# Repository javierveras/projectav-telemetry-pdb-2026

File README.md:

# Telemetry & Power Distribution System
Our power distribution and telemetry system's hardware, firmware, and technical documentation.

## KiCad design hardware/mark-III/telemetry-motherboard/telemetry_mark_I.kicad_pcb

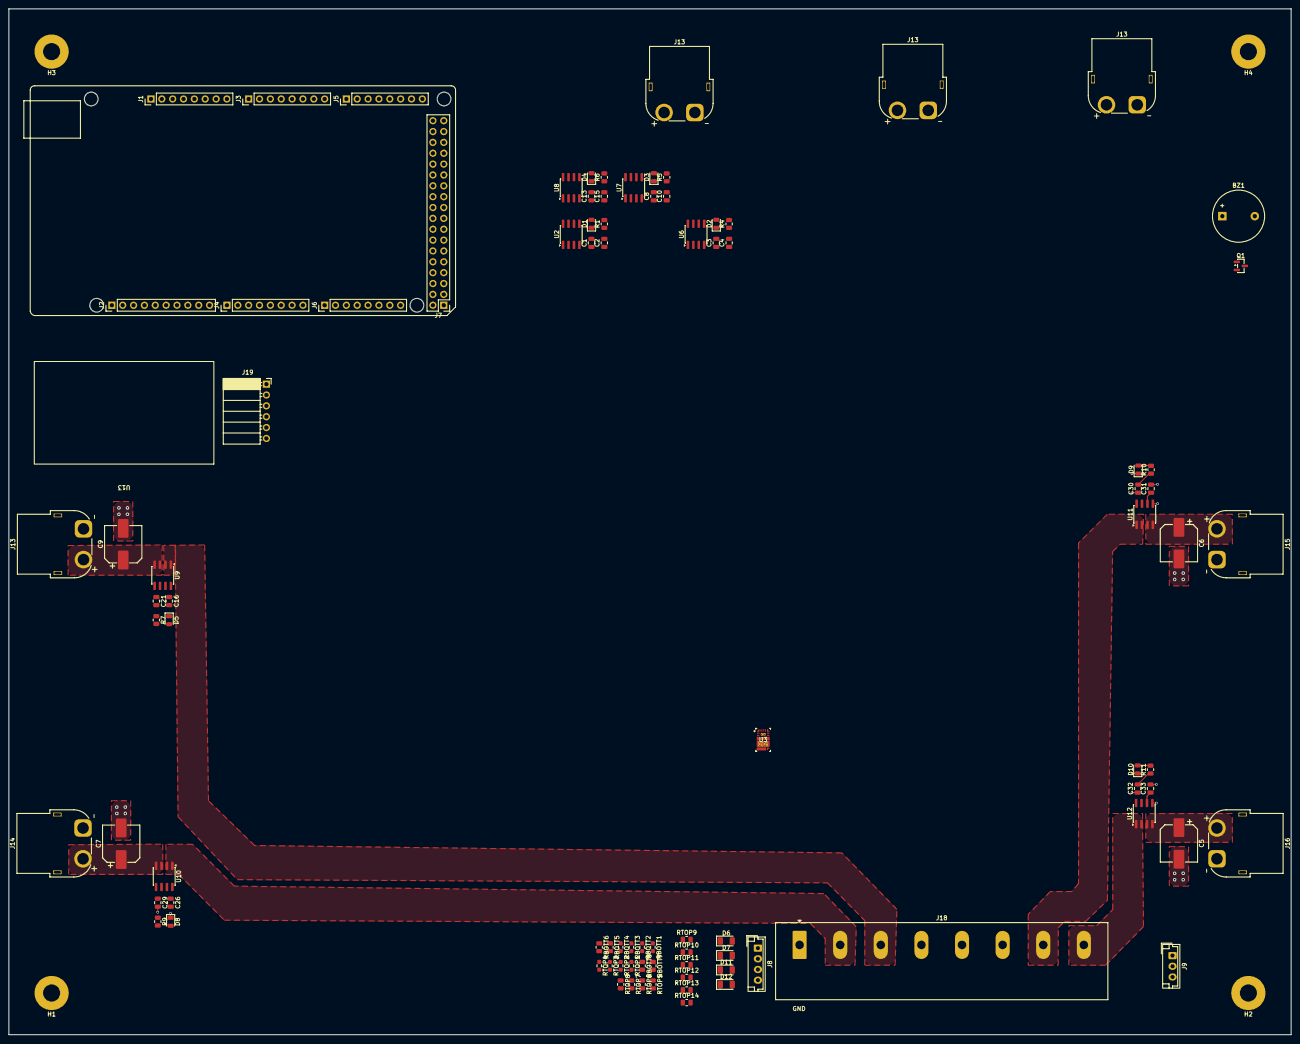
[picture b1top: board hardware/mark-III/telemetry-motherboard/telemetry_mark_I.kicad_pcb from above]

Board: 4 copper layers, 300.0 x 240.0 mm, 101 parts (0 on the bottom side), 58 nets.

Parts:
BZ1: Buzzer; Buzzer_12x9.5RM7.6
C1, C3, C8, C13, C16, C26, C30, C32: 100nF; C_0805_2012Metric
C2, C4, C10, C15, C21, C29, C31, C33: 1nF; C_0805_2012Metric
C5, C6, C7, C9: C_Polarized; CP_Elec_8x10.5
D1, D2, D3, D4, D5, D8, D9, D10: LED; LED_0805_2012Metric
D6, D7, D11, D12: LED; LED_1206_3216Metric
H1, H2, H3, H4: MountingHole; MountingHole_4mm_Pad
J1: Power; PinHeader_1x08_P2.54mm_Vertical
J2: PWM; PinHeader_1x10_P2.54mm_Vertical
J3, J5: Analog; PinHeader_1x08_P2.54mm_Vertical
J4: PWM; PinHeader_1x08_P2.54mm_Vertical
J6: Communication; PinHeader_1x08_P2.54mm_Vertical
J7: Digital; PinHeader_2x18_P2.54mm_Vertical
J8: INPUT_CELL1; JST_EH_B4B-EH-A_1x04_P2.50mm_Vertical
J9: Temp_Sensor_Header; JST_EH_B3B-EH-A_1x03_P2.50mm_Vertical
J13, J13#2, J13#3, J13#4, J14, J15, J16: Conn_01x02_Socket; AMASS_XT60PW-F_1x02_P7.20mm_Horizontal
J18: Screw_Terminal_01x08; TerminalBlock_Ningbo-Kagnex_HB9500_1x08_P9.5mm
J19: Conn_01x06_Pin; PinSocket_1x06_P2.54mm_Horizontal
MH1, MH2, MH5, MH6: MountingHole_3.2mm
Q1: Q_NPN_BEC; SOT-23
R1, R4, R5, R6, R7, R9, R10, R11: 1k; R_0805_2012Metric
RBOTT1, RBOTT2, RBOTT3, RBOTT4: 2k; R_0603_1608Metric_Pad0.98x0.95mm_HandSolder
RBOTT5, RBOTT6, RBOTT7, RBOTT8: 10K; R_0805_2012Metric
RTOP1, RTOP2, RTOP3, RTOP4: 18k; R_0603_1608Metric_Pad0.98x0.95mm_HandSolder
RTOP5, RTOP6, RTOP7, RTOP8: 47K; R_0805_2012Metric
RTOP9, RTOP12, RTOP13, RTOP14: 680; R_0805_2012Metric
RTOP10: 1k; R_0805_2012Metric
RTOP11: 10k; R_0805_2012Metric
U1: ArduinoMega
U2, U6, U7, U8, U9, U10, U11, U12: ACS712xLCTR-05B; SOIC-8_3.9x4.9mm_P1.27mm
U3: TPS543B25VRYSR; RYS0017A-MFG
U13: Untitled_3

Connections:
5V_MEASS: J9.1, RTOP4.1, U2.3 (IP-), U2.4 (IP-)
12V_MEASS: RTOP1.1, U6.3 (IP-), U6.4 (IP-)
24V_MEASS: RTOP2.1, U7.3 (IP-), U7.4 (IP-)
+5V: C1.2, C3.2, C8.2, C13.2, C16.2, C26.2, C30.2, C32.2, J1.5, J7.35, J7.36, R1.1, R4.1, R5.1, R6.1, R7.1, R9.1, R10.1, R11.1, U2.1 (IP+), U2.2 (IP+), U2.8 (VCC), U6.8 (VCC), U7.8 (VCC), U8.8 (VCC), U9.8 (VCC), U10.8 (VCC), U11.8 (VCC), U12.8 (VCC)
/5V_CURRENT: J3.1, U2.7 (VIOUT)
/5V_VOLTAGE: RBOTT4.1, RTOP4.2
/12V_CURRENT: J3.2, U6.7 (VIOUT)
/12V_VOLTAGE: RBOTT1.1, RTOP1.2
/24V_CURRENT: J3.3, U7.7 (VIOUT)
/24V_VOLTAGE: RBOTT2.1, RTOP2.2
/+12V: U6.1 (IP+), U6.2 (IP+)
/+24V: U7.1 (IP+), U7.2 (IP+)
/BATT_CURRENT: J3.4, U8.7 (VIOUT)
/BATT_VOLTAGE: RBOTT3.1, RTOP3.2
/BMS/MEASS_CELL1: RBOTT5.1, RTOP5.2
/BMS/MEASS_CELL2: RBOTT7.1, RTOP7.2
/BMS/MEASS_CELL3: RBOTT6.1, RTOP6.2
/BMS/MEASS_CELL4: RBOTT8.1, RTOP8.2
/RAW_BATT(15-ESCs): U8.1 (IP+), U8.2 (IP+)
/RAW_BATT(15-W1): J18.3, U9.1 (IP+), U9.2 (IP+)
/RAW_BATT(15-W2): J18.2, U10.1 (IP+), U10.2 (IP+)
/RAW_BATT(15-W3): J18.7, U11.1 (IP+), U11.2 (IP+)
/RAW_BATT(15-W4): J18.8, U12.1 (IP+), U12.2 (IP+)
/SCL/21: J2.1, J6.8
/SDA/20: J2.2, J6.7
/TEMP_READING: J3.5, J9.2
/W1_MEASS: C9.1, J13.2, J13#4.2, U9.3 (IP-), U9.4 (IP-)
/W2_MEASS: C7.1, J14.2, U10.3 (IP-), U10.4 (IP-)
/W3_MEASS: C6.1, J15.2, U11.3 (IP-), U11.4 (IP-)
/W4_MEASS: C5.1, J16.2, U12.3 (IP-), U12.4 (IP-)
BATT_MEASS: RTOP3.1, U8.3 (IP-), U8.4 (IP-)
GND: C1.1, C2.2, C3.1, C4.2, C5.2, C6.2, C7.2, C8.1, C9.2, C10.2, C13.1, C15.2, C16.1, C21.2, C26.1, C29.2, C30.1, C31.2, C32.1, C33.2, D1.1 (K), D2.1 (K), D3.1 (K), D4.1 (K), D5.1 (K), D6.1 (K), D7.1 (K), D8.1 (K), D9.1 (K), D10.1 (K), D11.1 (K), D12.1 (K), J1.6, J1.7, J2.4, J7.1, J7.2, J9.3, J13.1, J13#4.1, J14.1, J15.1, J16.1, J18.1, Q1.2 (E), RBOTT1.2, RBOTT2.2, RBOTT3.2, RBOTT4.2, RBOTT5.2, RBOTT6.2, RBOTT7.2, RBOTT8.2, RTOP11.1, U2.5 (GND), U6.5 (GND), U7.5 (GND), U8.5 (GND), U9.5 (GND), U10.5 (GND), U11.5 (GND), U12.5 (GND)
unnamed: BZ1.2 (-), Q1.3 (C)
unnamed: D1.2 (A), R1.2
unnamed: D2.2 (A), R4.2
unnamed: D3.2 (A), R5.2
unnamed: D4.2 (A), R6.2
unnamed: D5.2 (A), R7.2
unnamed: D6.2 (A), RTOP9.2
unnamed: D7.2 (A), RTOP13.2
unnamed: D8.2 (A), R9.2
unnamed: D9.2 (A), R10.2
unnamed: D10.2 (A), R11.2
unnamed: D11.2 (A), RTOP12.2
unnamed: D12.2 (A), RTOP14.2
unnamed: Q1.1 (B), RTOP10.2, RTOP11.2
unnamed: C2.1, U2.6 (FILTER)
unnamed: C4.1, U6.6 (FILTER)
unnamed: C10.1, U7.6 (FILTER)
unnamed: C15.1, U8.6 (FILTER)
unnamed: C21.1, U9.6 (FILTER)
unnamed: C29.1, U10.6 (FILTER)
unnamed: C31.1, U11.6 (FILTER)
unnamed: C33.1, U12.6 (FILTER)
RAW_CELL1: J8.1, RTOP5.1
RAW_CELL2: J8.2, RTOP7.1
RAW_CELL3: J8.3, RTOP6.1
RAW_CELL4: J8.4, RTOP8.1

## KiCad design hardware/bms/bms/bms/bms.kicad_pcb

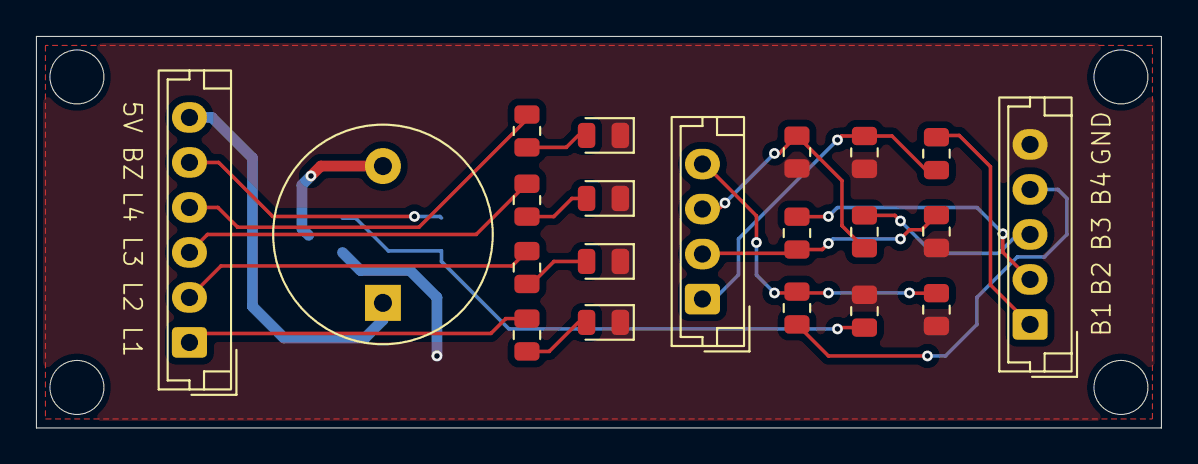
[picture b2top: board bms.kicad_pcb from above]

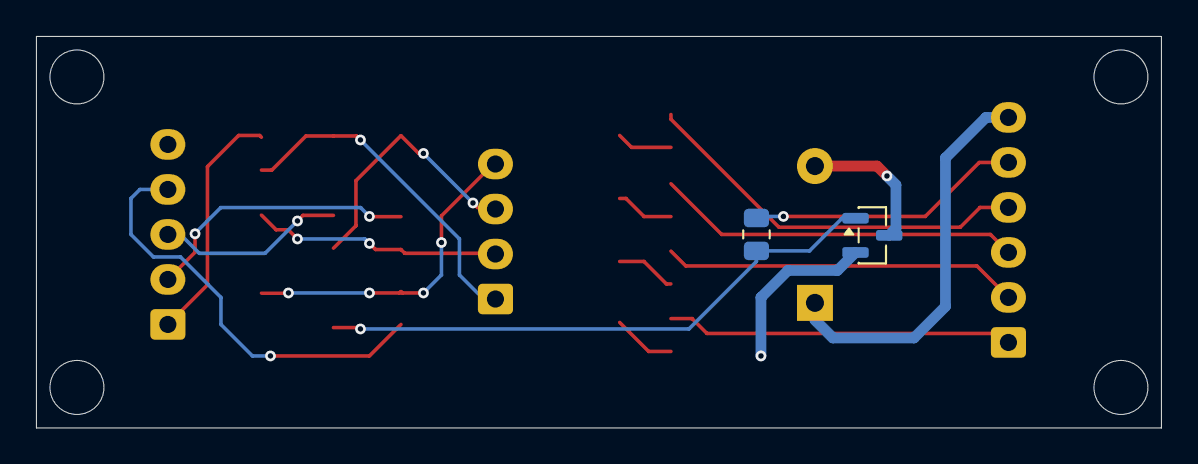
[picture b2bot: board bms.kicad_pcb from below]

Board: 2 copper layers, 62.5 x 21.8 mm, 23 parts (2 on the bottom side), 21 nets.

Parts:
BZ1: Buzzer; Buzzer_12x9.5RM7.6
D1, D2, D3, D4: LED; LED_0805_2012Metric
J1: OUTPUT; JST_EH_B4B-EH-A_1x04_P2.50mm_Vertical
J2: Conn_01x05_Pin; JST_EH_B5B-EH-A_1x05_P2.50mm_Vertical
J3: Conn_01x06_Pin; JST_EH_B6B-EH-A_1x06_P2.50mm_Vertical
Q1: Q_NPN_BEC; SOT-23
RBOTT5, RBOTT6, RBOTT7, RBOTT8: 10K; R_0805_2012Metric
RTOP5, RTOP6, RTOP7, RTOP8: 47K; R_0805_2012Metric
RTOP9, RTOP12, RTOP13, RTOP14: 680; R_0805_2012Metric
RTOP10: 1k; R_0805_2012Metric
RTOP11: 10k; R_0805_2012Metric

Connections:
/5V: BZ1.1 (+), J3.6
/BUZZER_GATE: J3.5, RTOP10.1
/LED1: J3.1, RTOP9.1
/LED2: J3.2, RTOP13.1
/LED3: J3.3, RTOP14.1
/LED4: J3.4, RTOP12.1
/MEASS_CELL1: J1.1, RBOTT5.1, RTOP5.2
/MEASS_CELL2: J1.2, RBOTT7.1, RTOP7.2
/MEASS_CELL3: J1.3, RBOTT6.1, RTOP6.2
/MEASS_CELL4: J1.4, RBOTT8.1, RTOP8.2
GND: D1.1 (K), D2.1 (K), D3.1 (K), D4.1 (K), J2.5, Q1.2 (E), RBOTT5.2, RBOTT6.2, RBOTT7.2, RBOTT8.2, RTOP11.1
unnamed: BZ1.2 (-), Q1.3 (C)
unnamed: D1.2 (A), RTOP9.2
unnamed: D2.2 (A), RTOP12.2
unnamed: D3.2 (A), RTOP13.2
unnamed: D4.2 (A), RTOP14.2
unnamed: Q1.1 (B), RTOP10.2, RTOP11.2
RAW_CELL1: J2.1, RTOP5.1
RAW_CELL2: J2.2, RTOP7.1
RAW_CELL3: J2.3, RTOP6.1
RAW_CELL4: J2.4, RTOP8.1

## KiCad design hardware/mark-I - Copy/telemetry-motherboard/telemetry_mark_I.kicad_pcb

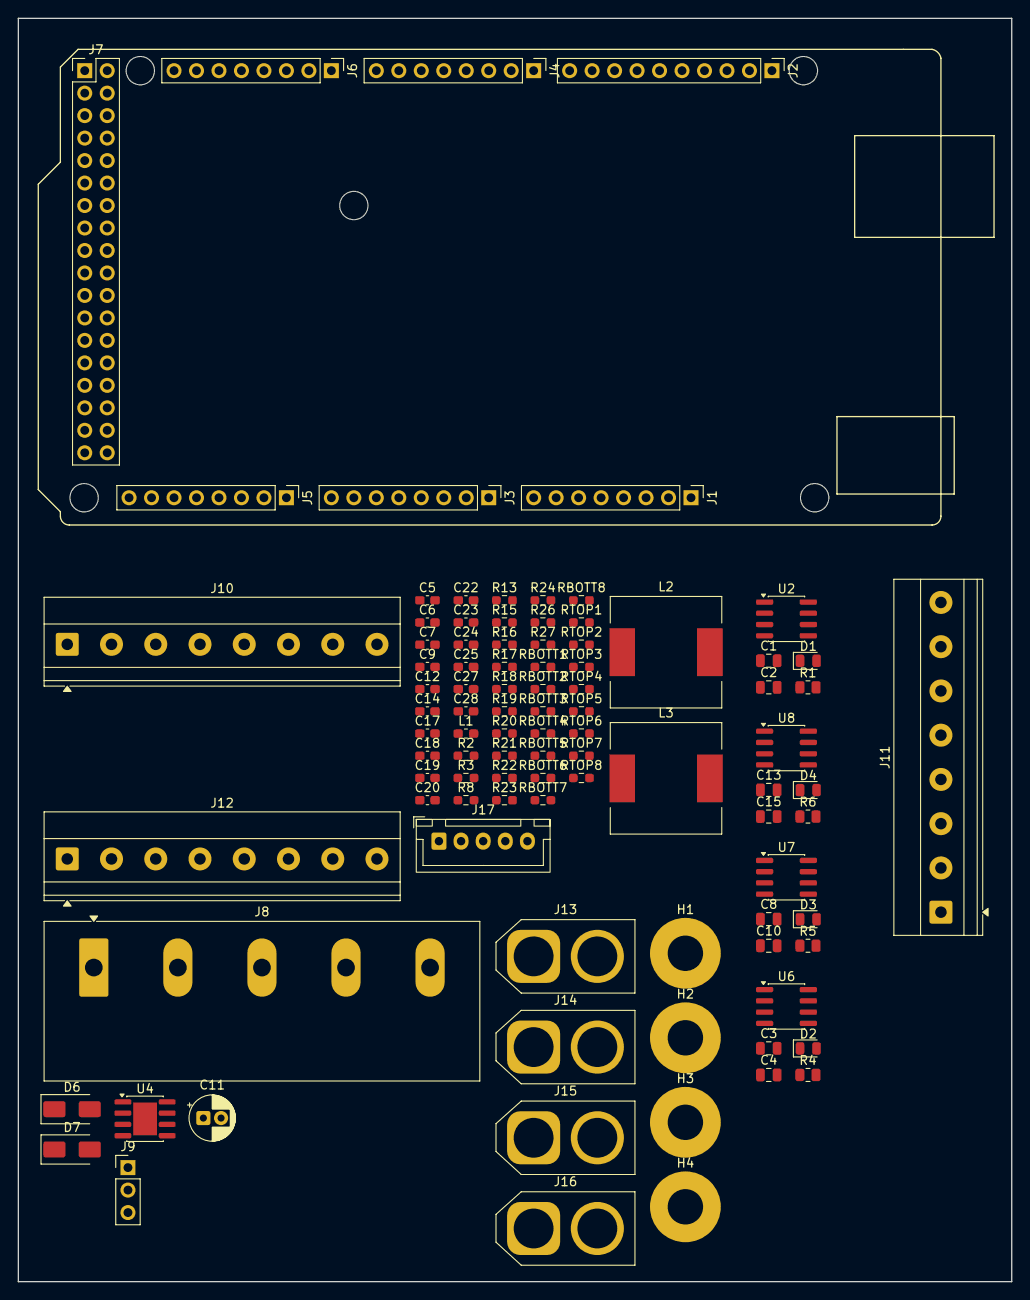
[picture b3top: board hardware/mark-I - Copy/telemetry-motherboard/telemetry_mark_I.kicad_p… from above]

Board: 2 copper layers, 112.2 x 142.8 mm, 101 parts (0 on the bottom side), 56 nets, no tracks yet.

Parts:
C1, C3, C8, C13: 100nF; C_0805_2012Metric
C2, C4, C10, C15: 1nF; C_0805_2012Metric
C5, C6: 68n; C_0603_1608Metric_Pad1.08x0.95mm_HandSolder
C7: 33n; C_0603_1608Metric_Pad1.08x0.95mm_HandSolder
C9: 4.7u; C_0603_1608Metric_Pad1.08x0.95mm_HandSolder
C11: 30u; CP_Radial_D5.0mm_P2.00mm
C12, C17, C19, C27, C28: 10u; C_0603_1608Metric_Pad1.08x0.95mm_HandSolder
C14: 4.7n; C_0603_1608Metric_Pad1.08x0.95mm_HandSolder
C18, C20: 0.3n; C_0603_1608Metric_Pad1.08x0.95mm_HandSolder
C22, C23: 1n; C_0603_1608Metric_Pad1.08x0.95mm_HandSolder
C24, C25: 100n; C_0603_1608Metric_Pad1.08x0.95mm_HandSolder
D1, D2, D3, D4: LED; LED_0805_2012Metric
D6, D7: SS54; D_SMA
H1, H2, H3, H4: MountingHole; MountingHole_4mm_Pad
J1: Power; PinHeader_1x08_P2.54mm_Vertical
J2: PWM; PinHeader_1x10_P2.54mm_Vertical
J3, J5: Analog; PinHeader_1x08_P2.54mm_Vertical
J4: PWM; PinHeader_1x08_P2.54mm_Vertical
J6: Communication; PinHeader_1x08_P2.54mm_Vertical
J7: Digital; PinHeader_2x18_P2.54mm_Vertical
J8: Input_Terminal; TerminalBlock_Ningbo-Kagnex_HB9500_1x05_P9.5mm
J9: Temp_Sensor_Header; PinHeader_1x03_P2.54mm_Vertical
J10: 5V_BUS; TerminalBlock_Phoenix_MKDS-1,5-8_1x08_P5.00mm_Horizontal
J11: 12V_BUS; TerminalBlock_Phoenix_MKDS-1,5-8_1x08_P5.00mm_Horizontal
J12: 24V_BUS; TerminalBlock_Phoenix_MKDS-1,5-8_1x08_P5.00mm_Horizontal
J13, J14, J15, J16: Conn_01x02_Socket; AMASS_XT60-F_1x02_P7.20mm_Vertical
J17: BMS_Header; JST_XH_B5B-XH-A_1x05_P2.50mm_Vertical
L1: 6.8u; L_0603_1608Metric_Pad1.05x0.95mm_HandSolder
L2, L3: 22u; L_12x12mm_H8mm
MH1, MH2, MH3, MH5, MH6: MountingHole_3.2mm
R1, R4, R5, R6: 1k; R_0805_2012Metric
R2: 20k; R_0603_1608Metric_Pad0.98x0.95mm_HandSolder
R3: 120k; R_0603_1608Metric_Pad0.98x0.95mm_HandSolder
R8: 2.8M; R_0603_1608Metric_Pad0.98x0.95mm_HandSolder
R13: 27.4k; R_0603_1608Metric_Pad0.98x0.95mm_HandSolder
R15: 43.2k; R_0603_1608Metric_Pad0.98x0.95mm_HandSolder
R16, R26: 105k; R_0603_1608Metric_Pad0.98x0.95mm_HandSolder
R17, R18: 47k; R_0603_1608Metric_Pad0.98x0.95mm_HandSolder
R19, R21: 680k; R_0603_1608Metric_Pad0.98x0.95mm_HandSolder
R20, R22: 100k; R_0603_1608Metric_Pad0.98x0.95mm_HandSolder
R23: 52.3k; R_0603_1608Metric_Pad0.98x0.95mm_HandSolder
R24: 10k; R_0603_1608Metric_Pad0.98x0.95mm_HandSolder
R27: 7.5k; R_0603_1608Metric_Pad0.98x0.95mm_HandSolder
RBOTT1, RBOTT2, RBOTT3, RBOTT4: 2k; R_0603_1608Metric_Pad0.98x0.95mm_HandSolder
RBOTT5, RBOTT6, RBOTT7, RBOTT8: 10K; R_0603_1608Metric_Pad0.98x0.95mm_HandSolder
RTOP1, RTOP2, RTOP3, RTOP4: 18k; R_0603_1608Metric_Pad0.98x0.95mm_HandSolder
RTOP5, RTOP6, RTOP7, RTOP8: 47K; R_0603_1608Metric_Pad0.98x0.95mm_HandSolder
U2, U6, U7, U8: ACS712xLCTR-05B; SOIC-8_3.9x4.9mm_P1.27mm
U4: AOZ1284PI; SOIC-8-1EP_3.9x4.9mm_P1.27mm_EP2.71x3.7mm

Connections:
5V_MEASS: J9.1, J10.1, J10.2, J10.3, J10.4, J10.5, J10.6, J10.7, J10.8, RTOP4.1, U2.3 (IP-), U2.4 (IP-)
12V_MEASS: J11.1, J11.2, J11.3, J11.4, J11.5, J11.6, J11.7, J11.8, RTOP1.1, U6.3 (IP-), U6.4 (IP-)
24V_MEASS: J12.1, J12.2, J12.3, J12.4, J12.5, J12.6, J12.7, J12.8, RTOP2.1, U7.3 (IP-), U7.4 (IP-)
+5V: C1.2, C3.2, C8.2, C13.2, C27.1, J1.5, J7.35, J7.36, L2.2, R1.1, R4.1, R5.1, R6.1, R23.1, U2.1 (IP+), U2.2 (IP+), U2.8 (VCC), U6.8 (VCC), U7.8 (VCC), U8.8 (VCC)
+12V: C28.1, L3.2, R26.1, U6.1 (IP+), U6.2 (IP+)
+24V: C11.1, R8.2, U7.1 (IP+), U7.2 (IP+)
/5V_CURRENT: J3.1, U2.7 (VIOUT)
/5V_VOLTAGE: RBOTT4.1, RTOP4.2
/12V_CURRENT: J3.2, U6.7 (VIOUT)
/12V_VOLTAGE: RBOTT1.1, RTOP1.2
/24V_CURRENT: J3.3, U7.7 (VIOUT)
/24V_VOLTAGE: RBOTT2.1, RTOP2.2
/BATT_CURRENT: J3.4, U8.7 (VIOUT)
/BATT_VOLTAGE: RBOTT3.1, RTOP3.2
/MEASS_CELL1: J3.6, RBOTT5.1, RTOP5.2
/MEASS_CELL2: J3.7, RBOTT7.1, RTOP7.2
/MEASS_CELL3: J3.8, RBOTT6.1, RTOP6.2
/MEASS_CELL4: J5.1, RBOTT8.1, RTOP8.2
/RAW_BATT(15-5): C17.1, J8.1, R19.1, U4.9 (VIN)
/RAW_BATT(15-12): C19.1, J8.2, R21.1
/RAW_BATT(15-24): C12.1, J8.3
/RAW_BATT(15-ESCs): J8.4, U8.1 (IP+), U8.2 (IP+)
/SCL/21: J2.1, J6.8
/SDA/20: J2.2, J6.7
/TEMP_READING: J3.5, J9.2
BATT_MEASS: J13.1, J14.1, J15.1, J16.1, RTOP3.1, U8.3 (IP-), U8.4 (IP-)
GND: C1.1, C2.2, C3.1, C4.2, C7.2, C8.1, C9.2, C10.2, C11.2, C12.2, C13.1, C15.2, C17.2, C19.2, C22.2, C23.2, C27.2, C28.2, D1.1 (K), D2.1 (K), D3.1 (K), D4.1 (K), D6.2 (A), D7.2 (A), J1.6, J1.7, J2.4, J7.1, J7.2, J9.3, J13.2, J14.2, J15.2, J16.2, R2.2, R3.1, R13.2, R15.2, R16.2, R17.2, R18.2, R20.2, R22.2, R24.2, R27.2, RBOTT1.2, RBOTT2.2, RBOTT3.2, RBOTT4.2, RBOTT5.2, RBOTT6.2, RBOTT7.2, RBOTT8.2, U2.5 (GND), U4.3 (GND), U6.5 (GND), U7.5 (GND), U8.5 (GND)
unnamed: C14.2, R13.1
unnamed: C18.1, R15.1
unnamed: C20.1, R16.1
unnamed: D1.2 (A), R1.2
unnamed: D2.2 (A), R4.2
unnamed: D3.2 (A), R5.2
unnamed: D4.2 (A), R6.2
unnamed: C24.2, D6.1 (K), L2.1, U4.1 (LX)
unnamed: C25.2, D7.1 (K), L3.1
unnamed: C2.1, U2.6 (FILTER)
unnamed: R3.2, R8.1
unnamed: C7.1, R2.1
unnamed: C6.1, L1.2
unnamed: C5.1, L1.1
unnamed: C24.1, U4.2 (BST)
unnamed: C18.2, U4.5 (COMP)
unnamed: R19.2, R20.1, U4.8 (EN)
unnamed: R23.2, R24.1, U4.6 (FB)
unnamed: R17.1, U4.4 (FSW)
unnamed: C22.1, U4.7 (SS)
unnamed: R21.2, R22.1
unnamed: R26.2, R27.1
unnamed: C4.1, U6.6 (FILTER)
unnamed: C10.1, U7.6 (FILTER)
unnamed: C15.1, U8.6 (FILTER)
RAW_CELL1: J17.1, RTOP5.1
RAW_CELL2: J17.2, RTOP7.1
RAW_CELL3: J17.3, RTOP6.1
RAW_CELL4: J17.4, RTOP8.1
